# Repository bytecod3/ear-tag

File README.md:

# ear-tag
Ear tag with LORA

## Introduction 
This proejct implements a catle ear tag using LORA technology. The purpose of the tag is to monitor location and activity of the 
cattle. It is tailored to open ranch setups where the cattle have a huge chunk of land to graze.

This ear tag also monitors the activity level of the cattle and uses a custom algrithm to detect shcok and abnormal vibrations 
to tell whether the animal fell, is still lying down etc.

## How it works
The device reads accelerations from an accelerometer sensor and does data processing to translate them into useful data like shock and activity levels.
Using a GPS, we can monitor the real-time location of the animal. 

This data is transmitted to a base station via a LORA gateway and visualized on the farmer's device, either 
phone and/or desktop setup.

## Measuring acceleration and activity monitoring
MPU6050 measures acceleration using its on-chip accelerometer with four programmable full scale ranges of ±2g, ±4g, ±8g and ±16g that can be set by the user.The X, Y and Z are relative to how the chip sits on the module as shown to the right and will ultimately be dependent on the orientation of the module 
on the device.

### Measuring rotation 
MPU6050 measures rotation using its on-chip gyroscope with four programmable full scale ranges of ±250°/s, ±500°/s, ±1000°/s and ±2000°/s that can be set by the user. The axis of rotation are relative the the X,Y and Z shown to the right.

### Using the I2C Interface
The module uses I2C interface for communications with MCU.It supports two different I2C addresses;0x68 and 0x69.That allows two devices to be used on the same bus or in case there is an address conflict with another device on the bus. The AD0 pin determines the I2C address to use.This pin has built in 4.7k pull-down resistor on module.if the pin is left unconnected,the line will be pulled low and the default I2C address will be 0X68.To select 0x69, connect the ADO pin to 3.3V. The SCL and SDA pins connect to A5 and A4 pins in analog input pins on the arduino board. The Auxiliary I2C address with pins labeled EDA and ECL are an I2C bus controlled by the MPU-9250 so that it can communicate directly with other sensors so that it can get additional information for its internal computations.

### Pitch and roll calculation 
Acceleration is read from all axes(x, y, z). The read values are then used to calculate the pitch and roll angles as shown below.

#### Pitch calculation
```c
pitch = 180 * atan2(accelX, sqrt(accelY*accelY + accelZ*accelZ))/PI 
```

#### Roll calculation 
```c
roll = 180 * atan2(accelY,sqrt(accelX*accelX + accelZ*accelZ))/PI
```

### Filtering and correcting MPU6050 data for accuracy 
After obtaining MPU6050 accelerometer and gyroscope readings, addressing sensor drift, noise, and measurement errors is essential for accurate motion tracking and orientation estimation. [1]

Animal exhibit distinct diurnal patterns depending on the time of day[2]. This means that in the morning and evening they show high activity but during nightime they are ruminating and therefore low activiy.  To detect the shocks, a High pass filter(HPF) is used to discard all data/noise below a given cutoff frequency. 

#### Complementary filter
This ear tag uses a simple complemetary filter to do the data cleanup especially when calulating the pitch and roll angles. 
The formula is shown below: 

```c
angle = alpha * (accelerometer_value + gyroscope_value * dt) + (1 - alpha)* accelerometer_value

```

The graph shows the results obtained from applying this complementary filter:

The red line shows the filtered pitch angle while the blue line shows the raw pitch angle.

#### Moving average filter
The moving average filter is used to smooth out acceleration values to remove high frequency noise. It averages the last N values and returns a cleaner value. This filter is used when we do not have big memory constraints and at the same time we need to implement basic filtering. 

```
/* pseudo code */

create a buffer  
read sensor  
store the previous N values 
calculate the average of the values 
return the average 
```

The acceleration values are prone to high frequency noise therefore the average filter was applied to them. The image below shows the result of filtering the x acceration:

The blue line shows the raw unfiltered value. Red line shows the filterd value. As it can be seen, the moving average filter works as expected, removing high frequency noise from the acceleration value.

## Shock detection 
In case the animal falls, we can use the MPU6050 to detect the shock and apply corrective measures. The accelerometer used is configured to measure up to (+/-)16g range.

### Resultant acceleration calculation 
To be able to register sudden animal activity, we have to keep track of the resultant acceleration, also called the magnitude of acceleration. The graph below shows the valeus of the raw magnitude of acceleration(using raw unfiltered values):

The sharp spikes show the acceleration when the device is dropped from about 40 cm high. It can clearly be seen that the magnitude of acceleration is high when this occurs.  

This next figure shows the resultant acceleration using raw and filtered acceleration values, combined into a single plot.

The red line shows the cleaner values obtained from the accelerometer.

By monitoring the value of this acceleration, we can be able to set a threshold that we then check to determine if there is a sudden upsurge of activity.

## Real Time animal tracking with GPS 
To track the animal in real time we emply a NEO6M GPS module that read the GPS location data. The data read from GPS is:  
- latitude
- longitude
- day
- month
- year
- minute 
- second 

This data is then packaged into a packet to make it easier for transmission. 
The GPS is read at a frequency defined by the DATA_UPDATE frequency value.

## LORA packet structure
| Field Name              | Data Type    | Description                     |
|-------------------------|--------------|---------------------------------|
| **tag_id**              | `uint32_t`   | Unique identifier for the tag   |
| **mode**                | `uint8_t`    | `0` = Operational, `1` = Simulation |
| **day**                 | `uint8_t`    | Day (1-31)                      |
| **month**               | `uint8_t`    | Month (1-12)                    |
| **year**                | `uint16_t`   | Year (e.g., 2025)               |
| **hour**                | `uint8_t`    | Hour (0-23)                     |
| **minute**              | `uint8_t`    | Minute (0-59)                   |
| **second**              | `uint8_t`    | Second (0-59)                   |
| **latitude**            | `float`      | GPS latitude in degrees         |
| **longitude**           | `float`      | GPS longitude in degrees        |
| **geo_fence_proximity** | `uint8_t`    | Proximity to geofence (0-100%)  |
| **acceleration_x**      | `float`      | X-axis acceleration (m/s²)     |
| **acceleration_y**      | `float`      | Y-axis acceleration (m/s²)     |
| **acceleration_z**      | `float`      | Z-axis acceleration (m/s²)     |
| **acceleration_magnitude** | `float`  | √(x² + y² + z²) (m/s²)        |

## Network and WiFi Provisioning
The device is configured to search for available networks and connect to them automatically.   To do this, we implement a WIFI provisioning scheme that allows you to connect to the network you desire. 

Follow the steps below to connect:

- once the device is powered on, it will create a WIFI netwoek called "EAR-TAG-WIFI", whose password is "password".
- Using your phone or PC, connect to this network.
- Once connected, open your browser and type the following IP address"
```
192.168.4.1
```

- A page with buttons will open up.
- Click on "Configure WIFI". A list of available networks will be shown. (Also here you can type teh SSID or password of the network that you will create, assuming you are using only one device)
- click on save
- The device will reboot itself and save the network accordingly.

## connecting to server
This section defiens the steps to connect tot the server. The server is built using with NodeJS and runs a MongoDB database. 

1. Install NodeJS, open the ```web app``` folder in terminal 
2. Run the following command.
```c
nodemon server.js
```
3. To get the IP address of the server, run the following command in terminal of your host machine 
```
ipconfig
```

Now to make the ear-tag-device connect to the server, make sure the PC amd the ear tag are on the same network using the WIFI 
connection procedures listed above. 

### Update the server URL in code
Since this is not a production environment and we have dynamic IP addresses, we need to update our server IP address in the Ear-tag firmware. Locate the server line below in the firmware and change to:

```c
const char* server_url = "http://YOUR_IP_ADDRESS:3000/api/location";

```
Replace with your IP address.

Upload the code the device and restart.

## Schematics 

## PCB designs
The PCBs are designed using EasyEDA Pro. Please download EasyEDA Pro here -> https://easyeda.com/page/download

## 3D casing designs 

## Viewing the system flowcharts and diagrams
To open the flowcharts and diagrams, download draw.io app here -> https://github.com/jgraph/drawio-desktop/releases/tag/v25.0.2
Choose the WindowsInstaller version

### References
[1] 
[2] [text](https://www.mdpi.com/2076-2615/14/2/301)

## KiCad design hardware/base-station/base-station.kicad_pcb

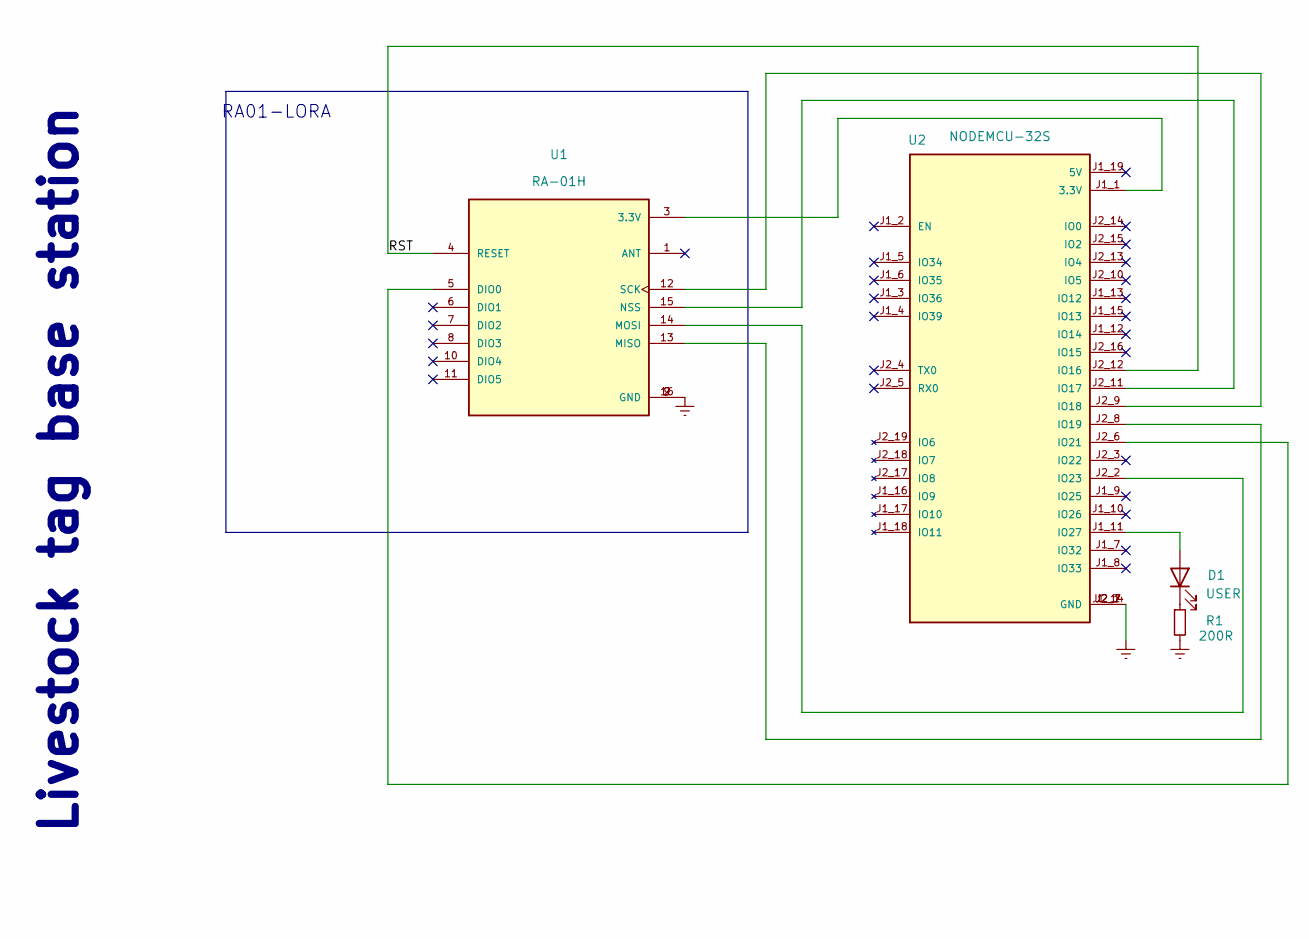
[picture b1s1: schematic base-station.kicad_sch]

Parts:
D1: USER; LED_D3.0mm
R1: 200R; R_Axial_DIN0207_L6.3mm_D2.5mm_P15.24mm_Horizontal
U1: RA-01H; XCVR_RA-01H; PARTREV V1.0
U2: NODEMCU-32S; MODULE_NODEMCU-32S; PARTREV V1

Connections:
/RST: U1.4 (RESET), U2.J2_12 (IO16)
Earth: R1.2, U1.2 (GND), U1.9 (GND), U1.16 (GND), U2.J1_14 (GND), U2.J2_1 (GND), U2.J2_7 (GND)
unnamed: D1.2 (A), U2.J1_11 (IO27)
unnamed: D1.1 (K), R1.1
unnamed: U1.3 (3.3V), U2.J1_1 (3.3V)
unnamed: U1.5 (DIO0), U2.J2_6 (IO21)
unnamed: U1.13 (MISO), U2.J2_8 (IO19)
unnamed: U1.14 (MOSI), U2.J2_2 (IO23)
unnamed: U1.15 (NSS), U2.J2_11 (IO17)
unnamed: U1.12 (SCK), U2.J2_9 (IO18)

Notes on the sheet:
Livestock tag base station
RA01-LORA

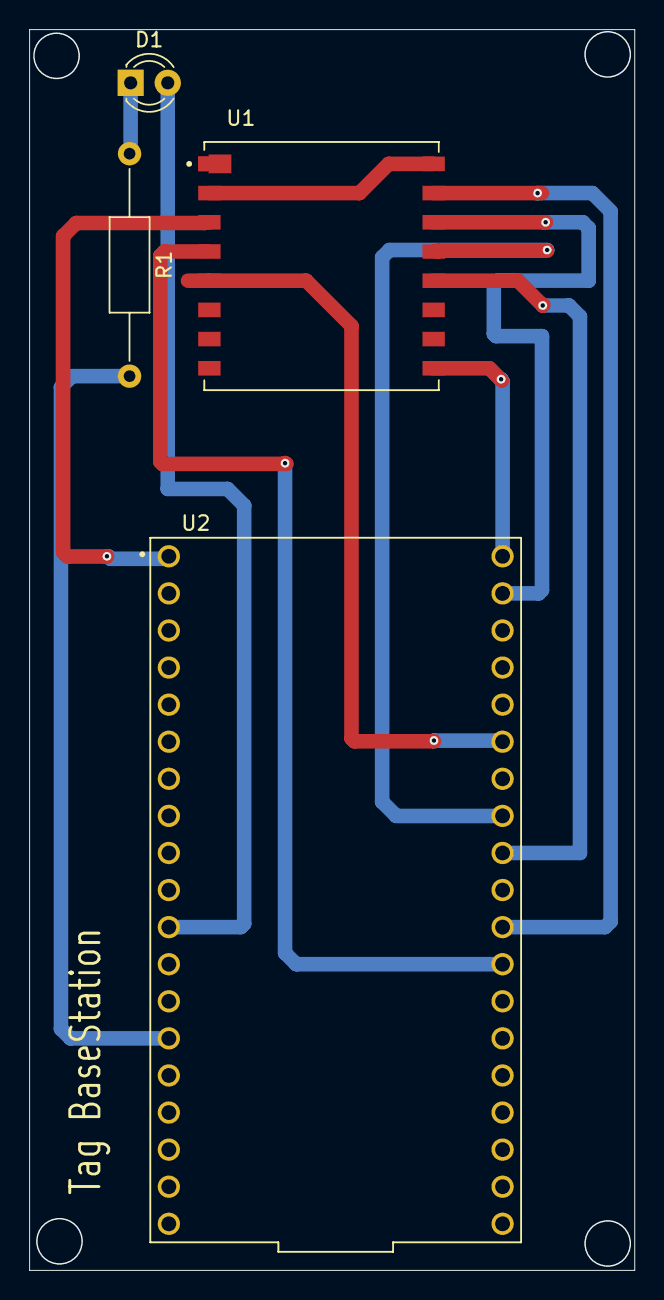
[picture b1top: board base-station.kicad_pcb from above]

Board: 2 copper layers, 41.5 x 85.0 mm, 4 parts (0 on the bottom side), 10 nets.

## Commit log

2024-12-21 init project structure
2024-12-21 updates README
2024-12-21 updated block diagram
2024-12-28 adds ear tag PCB
2024-12-30 adds base station
2025-02-10 adds tasks
2025-02-10 adds acceleration code-template
2025-02-26 [ADDS] mpu init
2025-02-26 ADDS 3D visualization
2025-02-26 [UPDATES] docs
2025-02-26 [UPDATES] complementary filter
2025-02-27 [UPDATES] filter
2025-02-27 [ADDS] filtered values
2025-03-03 [ADDS] GPS reading function
2025-03-03 [UDPATES] GPS sample frequency
2025-03-20 ADDS lora
2025-04-02 [FIXES] LORA pins
2025-04-03 ADDS button debounce
2025-04-03 [ADDS] base station LORA receive OK!
2025-04-03 [ADDS] working operational and simulation mdes
2025-04-03 [ADDS] packet structure
2025-04-05 [ADDS] leaflet map
2025-04-11 [Save to database]
2025-04-11 adds Correct server URL
2025-04-11 Updates DOCS
2025-04-15 updates app websockets
2025-04-15 updtes LEAFLET{'
2025-04-19 FIXES location data model name
2025-04-19 ADDS safe zones
2025-04-19 ADDS safety level zones
2025-04-19 ADDS safety levels
2025-04-19 UPDATES navbar
2025-04-20 FIXES device state check
2025-04-27 Updates SERVER URL
2025-04-27 updates notification
2025-05-18 ADDS led blink
